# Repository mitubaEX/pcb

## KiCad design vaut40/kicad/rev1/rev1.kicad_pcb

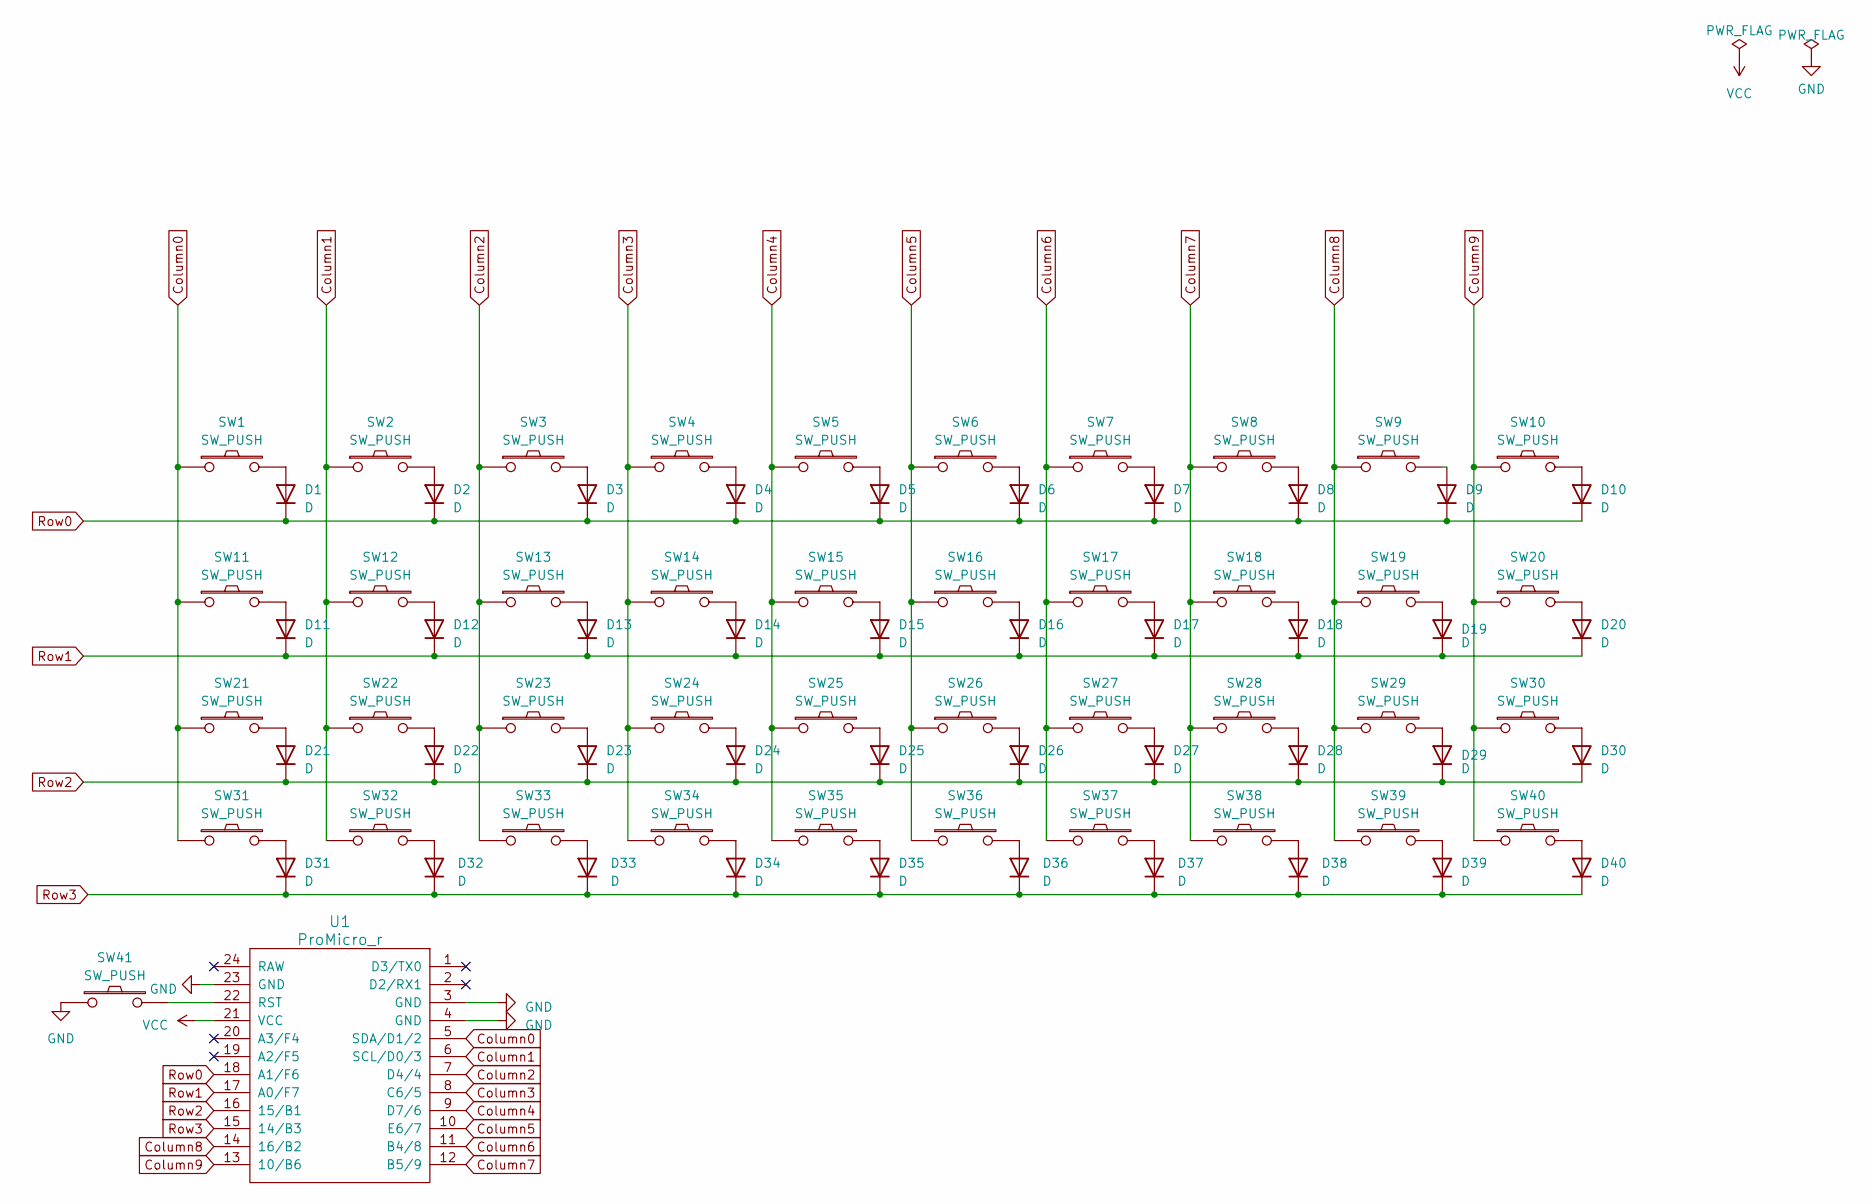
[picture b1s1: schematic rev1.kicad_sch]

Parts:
D1, D2, D3, D4, D5, D6, D7, D8, D9, D10, D11, D12, D13, D14, D15, D16, D17, D18, D19, D20, D21, D22, D23, D24, D25, D26, D27, D28, D29, D30, D31, D32, D33, D34, D35, D36, D37, D38, D39, D40: D; D3_SMD
SW1, SW2, SW3, SW4, SW5, SW6, SW7, SW8, SW9, SW10, SW11, SW12, SW13, SW14, SW15, SW16, SW17, SW18, SW19, SW20, SW21, SW22, SW23, SW24, SW25, SW26, SW27, SW28, SW29, SW30, SW31, SW32, SW33, SW34, SW35, SW36, SW37, SW38, SW39, SW40: SW_PUSH; CherryMX_Hotswap
SW41: SW_PUSH; ResetSW
U1: ProMicro_r; ProMicro_v3.5

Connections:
Column0: SW1.1, SW11.1, SW21.1, SW31.1, U1.5 (SDA/D1/2)
Column1: SW2.1, SW12.1, SW22.1, SW32.1, U1.6 (SCL/D0/3)
Column2: SW3.1, SW13.1, SW23.1, SW33.1, U1.7 (D4/4)
Column3: SW4.1, SW14.1, SW24.1, SW34.1, U1.8 (C6/5)
Column4: SW5.1, SW15.1, SW25.1, SW35.1, U1.9 (D7/6)
Column5: SW6.1, SW16.1, SW26.1, SW36.1, U1.10 (E6/7)
Column6: SW7.1, SW17.1, SW27.1, SW37.1, U1.11 (B4/8)
Column7: SW8.1, SW18.1, SW28.1, SW38.1, U1.12 (B5/9)
Column8: SW9.1, SW19.1, SW29.1, SW39.1, U1.14 (16/B2)
Column9: SW10.1, SW20.1, SW30.1, SW40.1, U1.13 (10/B6)
GND: SW41.1, U1.3 (GND), U1.4 (GND), U1.23 (GND)
unnamed: D1.2 (A), SW1.2
unnamed: D2.2 (A), SW2.2
unnamed: D3.2 (A), SW3.2
unnamed: D4.2 (A), SW4.2
unnamed: D5.2 (A), SW5.2
unnamed: D6.2 (A), SW6.2
unnamed: D7.2 (A), SW7.2
unnamed: D8.2 (A), SW8.2
unnamed: D9.2 (A), SW9.2
unnamed: D10.2 (A), SW10.2
unnamed: D11.2 (A), SW11.2
unnamed: D12.2 (A), SW12.2
unnamed: D13.2 (A), SW13.2
unnamed: D14.2 (A), SW14.2
unnamed: D15.2 (A), SW15.2
unnamed: D16.2 (A), SW16.2
unnamed: D17.2 (A), SW17.2
unnamed: D18.2 (A), SW18.2
unnamed: D19.2 (A), SW19.2
unnamed: D20.2 (A), SW20.2
unnamed: D21.2 (A), SW21.2
unnamed: D22.2 (A), SW22.2
unnamed: D23.2 (A), SW23.2
unnamed: D24.2 (A), SW24.2
unnamed: D25.2 (A), SW25.2
unnamed: D26.2 (A), SW26.2
unnamed: D27.2 (A), SW27.2
unnamed: D28.2 (A), SW28.2
unnamed: D29.2 (A), SW29.2
unnamed: D30.2 (A), SW30.2
unnamed: D31.2 (A), SW31.2
unnamed: D32.2 (A), SW32.2
unnamed: D33.2 (A), SW33.2
unnamed: D34.2 (A), SW34.2
unnamed: D35.2 (A), SW35.2
unnamed: D36.2 (A), SW36.2
unnamed: D37.2 (A), SW37.2
unnamed: D38.2 (A), SW38.2
unnamed: D39.2 (A), SW39.2
unnamed: D40.2 (A), SW40.2
unnamed: SW41.2, U1.22 (RST)
Row0: D1.1 (K), D2.1 (K), D3.1 (K), D4.1 (K), D5.1 (K), D6.1 (K), D7.1 (K), D8.1 (K), D9.1 (K), D10.1 (K), U1.18 (A1/F6)
Row1: D11.1 (K), D12.1 (K), D13.1 (K), D14.1 (K), D15.1 (K), D16.1 (K), D17.1 (K), D18.1 (K), D19.1 (K), D20.1 (K), U1.17 (A0/F7)
Row2: D21.1 (K), D22.1 (K), D23.1 (K), D24.1 (K), D25.1 (K), D26.1 (K), D27.1 (K), D28.1 (K), D29.1 (K), D30.1 (K), U1.16 (15/B1)
Row3: D31.1 (K), D32.1 (K), D33.1 (K), D34.1 (K), D35.1 (K), D36.1 (K), D37.1 (K), D38.1 (K), D39.1 (K), D40.1 (K), U1.15 (14/B3)
VCC: U1.21 (VCC)

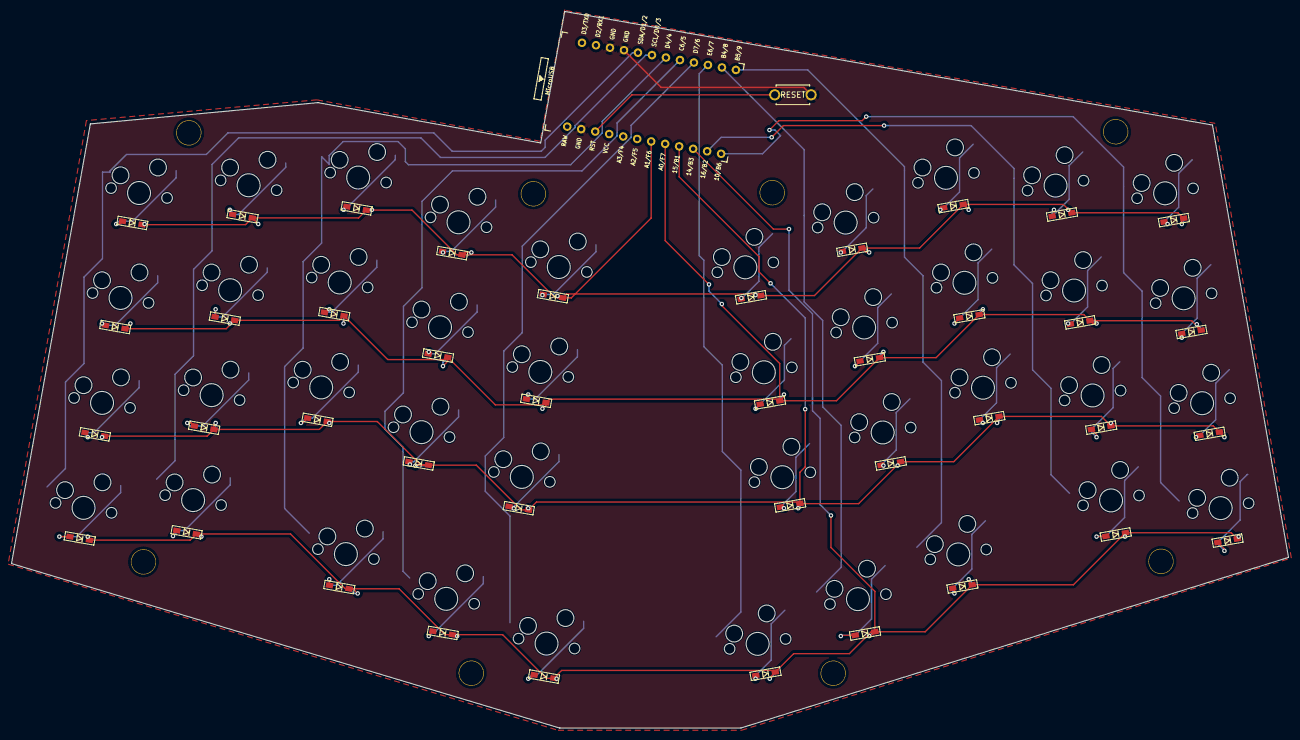
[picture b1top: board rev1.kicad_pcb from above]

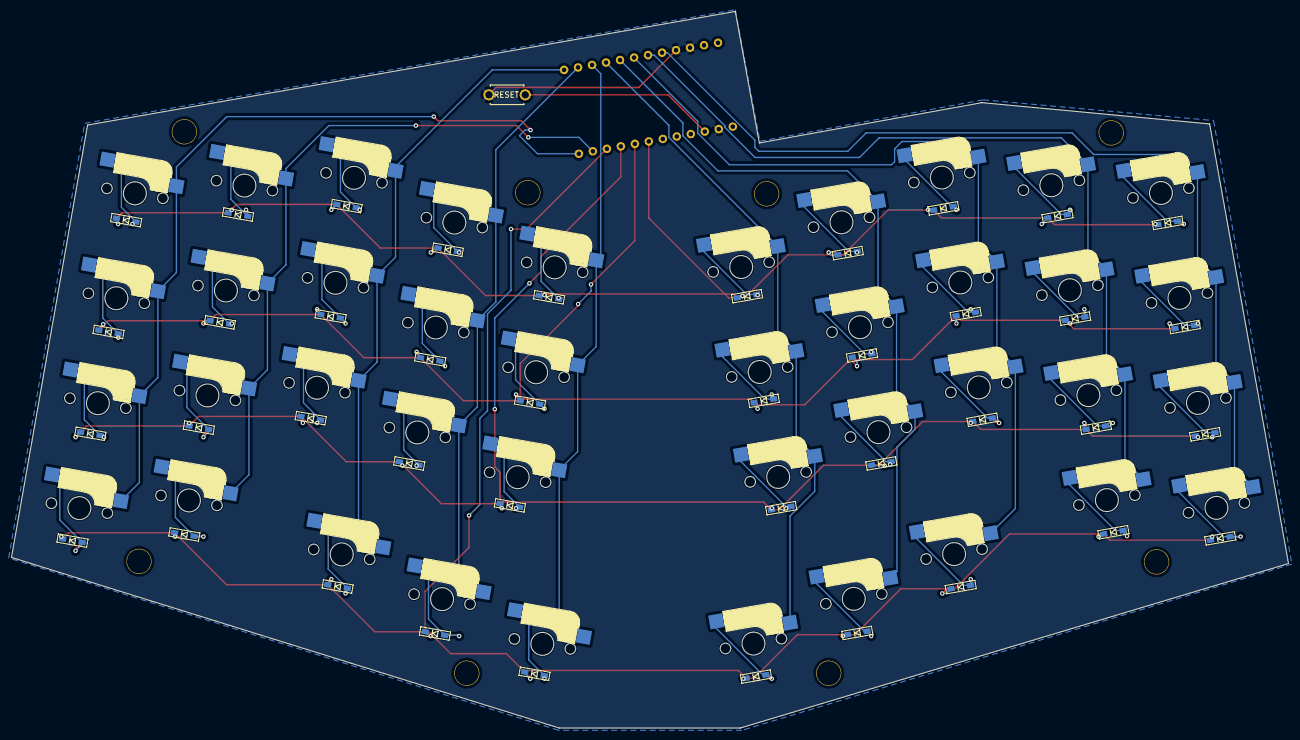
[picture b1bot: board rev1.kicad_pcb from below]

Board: 2 copper layers, 228.3 x 128.1 mm, 90 parts (40 on the bottom side), 56 nets.

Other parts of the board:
Ref**: Val**; m2_Spacer_Hole
Ref**#2, Ref**#3, Ref**#4, Ref**#5, Ref**#6, Ref**#7, Ref**#8: Val**; m2_Spacer_Hole

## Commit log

2023-05-01 add kle.json
2023-05-01 add kicad project
2023-05-01 add gitignore
2023-05-02 add firmware
2023-05-09 add ver2
2023-05-11 add ver2_top
2023-05-12 add ver2_bottom
2023-05-12 add gbr file
2023-05-29 add ver2.hex
2023-05-29 add zip file
2023-06-15 add vaut36 dir
2023-06-15 remove extra files
2023-06-15 fix gitignore
2023-08-22 add vaut40
2023-08-22 routing
2023-08-22 add top and bottom plate
2023-08-23 add hole
2023-08-23 add hole of top
2023-08-23 add hole of bottom
2023-08-23 add GND
2023-08-23 fix top plate
2023-08-29 fix error of pcb
